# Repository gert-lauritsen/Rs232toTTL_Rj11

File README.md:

ToDo

* Find connection to RJ11 connector
* Find 5V 
* Deside if resistor is necessarily (they are the for changing the PCB function)

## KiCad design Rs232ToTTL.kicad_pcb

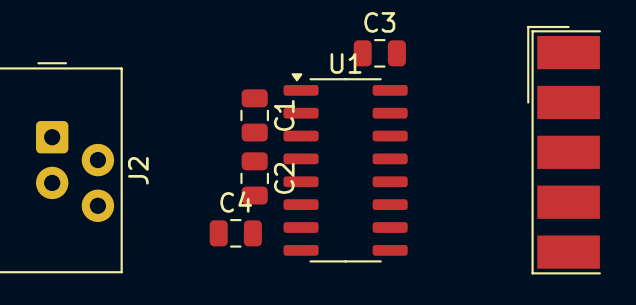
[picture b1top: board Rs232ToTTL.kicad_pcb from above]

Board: 2 copper layers, 7 parts (0 on the bottom side), 12 nets, no tracks yet.

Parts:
C1, C2, C3, C4: 100nF; C_0805_2012Metric
J1: DE9_Plug; DSUB-9_Female_EdgeMount_P2.77mm
J2: RJ9; RJ9_Evercom_5301-440xxx_Horizontal
U1: MAX232; SOIC-16_3.9x9.9mm_P1.27mm

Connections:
GND: C3.2, C4.2, J1.5, J2.1, U1.15 (GND)
unnamed: J1.7, J1.8
unnamed: C1.1, U1.1 (C1+)
unnamed: C1.2, U1.3 (C1-)
unnamed: C2.1, U1.4 (C2+)
unnamed: C2.2, U1.5 (C2-)
unnamed: J1.3, U1.13 (R1IN)
unnamed: J2.3, U1.12 (R1OUT)
unnamed: J1.6, U1.14 (T1OUT)
unnamed: J1.2, U1.7 (T2OUT)
unnamed: C3.1, U1.2 (VS+)
unnamed: C4.1, U1.6 (VS-)

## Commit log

2024-05-15 init
